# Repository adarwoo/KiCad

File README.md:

# KiCad
All KiCad projects

Adding all KiCad projects.

Currently, PCBs for the cnc (see Youtube guillaume.arreckx channel) are publised.

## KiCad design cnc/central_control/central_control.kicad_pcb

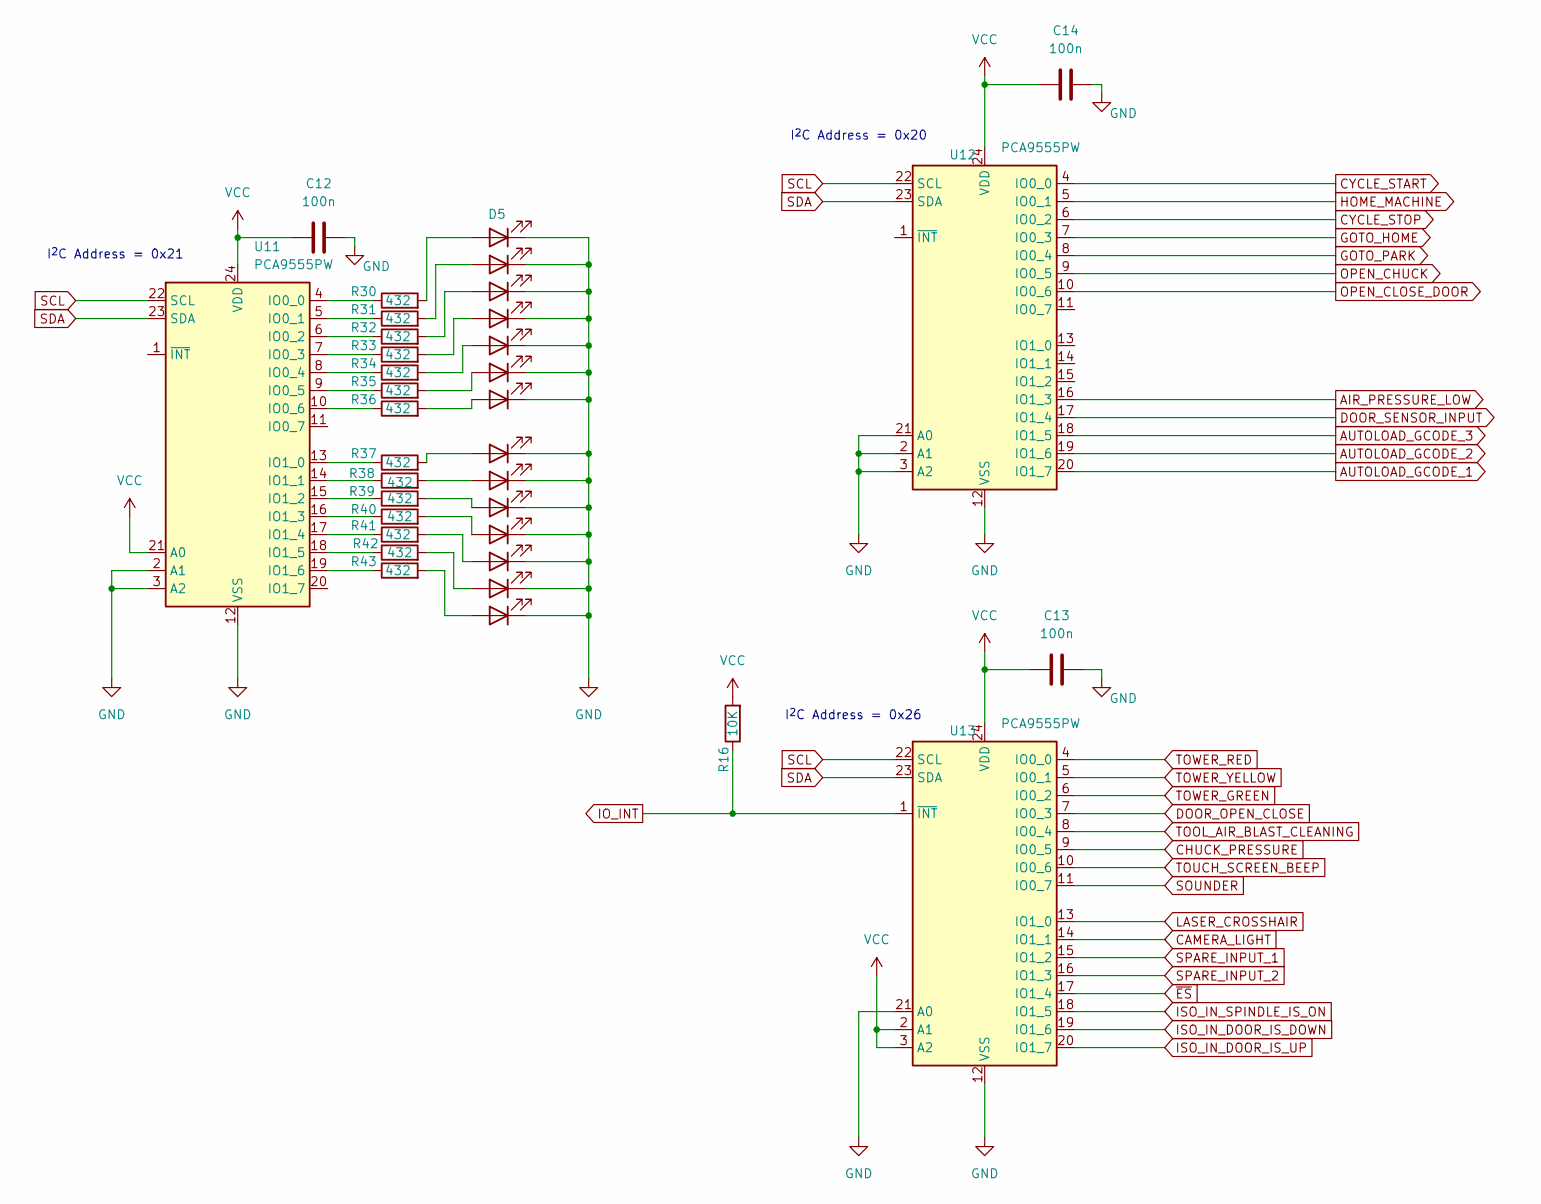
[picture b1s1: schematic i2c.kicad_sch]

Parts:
C12, C13, C14: 100n; C_0603_1608Metric_Pad1.08x0.95mm_HandSolder
D5: GRN; LED_D3.0mm
D6, D7, D8, D9, D10, D11, D12, D13, D14, D15, D16, D17, D18: LED; LED_D3.0mm
R16: 10K; R_1206_3216Metric_Pad1.30x1.75mm_HandSolder
R30, R31, R32, R33, R34, R35, R36, R37, R38, R39, R40, R41, R42, R43: 432; R_1206_3216Metric_Pad1.30x1.75mm_HandSolder
U11, U12, U13: PCA9555PW; TSSOP-24_4.4x7.8mm_P0.65mm

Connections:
AIR_PRESSURE_LOW: U12.16 (IO1_3); also elsewhere on the board
AUTOLOAD_GCODE_1: U12.20 (IO1_7); also elsewhere on the board
AUTOLOAD_GCODE_2: U12.19 (IO1_6); also elsewhere on the board
AUTOLOAD_GCODE_3: U12.18 (IO1_5); also elsewhere on the board
CAMERA_LIGHT: U13.14 (IO1_1); also elsewhere on the board
CHUCK_PRESSURE: U13.9 (IO0_5); also elsewhere on the board
CYCLE_START: U12.4 (IO0_0); also elsewhere on the board
CYCLE_STOP: U12.6 (IO0_2); also elsewhere on the board
DOOR_OPEN_CLOSE: U13.7 (IO0_3); also elsewhere on the board
DOOR_SENSOR_INPUT: U12.17 (IO1_4); also elsewhere on the board
GND: C12.2, C13.2, C14.2, D5.1 (K), D6.1 (K), D7.1 (K), D8.1 (K), D9.1 (K), D10.1 (K), D11.1 (K), D12.1 (K), D13.1 (K), D14.1 (K), D15.1 (K), D16.1 (K), D17.1 (K), D18.1 (K), U11.2 (A1), U11.3 (A2), U11.12 (VSS), U12.2 (A1), U12.3 (A2), U12.12 (VSS), U12.21 (A0), U13.12 (VSS), U13.21 (A0); also elsewhere on the board
GOTO_HOME: U12.7 (IO0_3); also elsewhere on the board
GOTO_PARK: U12.8 (IO0_4); also elsewhere on the board
HOME_MACHINE: U12.5 (IO0_1); also elsewhere on the board
ISO_IN_DOOR_IS_DOWN: U13.19 (IO1_6); also elsewhere on the board
ISO_IN_DOOR_IS_UP: U13.20 (IO1_7); also elsewhere on the board
ISO_IN_SPINDLE_IS_ON: U13.18 (IO1_5); also elsewhere on the board
LASER_CROSSHAIR: U13.13 (IO1_0); also elsewhere on the board
unnamed: D5.2 (A), R30.2
unnamed: D6.2 (A), R31.2
unnamed: D7.2 (A), R32.2
unnamed: D8.2 (A), R33.2
unnamed: D9.2 (A), R34.2
unnamed: D10.2 (A), R35.2
unnamed: D11.2 (A), R36.2
unnamed: D12.2 (A), R37.2
unnamed: D13.2 (A), R38.2
unnamed: D14.2 (A), R39.2
unnamed: D15.2 (A), R40.2
unnamed: D16.2 (A), R41.2
unnamed: D17.2 (A), R42.2
unnamed: D18.2 (A), R43.2
unnamed: R30.1, U11.4 (IO0_0)
unnamed: R31.1, U11.5 (IO0_1)
unnamed: R32.1, U11.6 (IO0_2)
unnamed: R33.1, U11.7 (IO0_3)
unnamed: R34.1, U11.8 (IO0_4)
unnamed: R35.1, U11.9 (IO0_5)
unnamed: R36.1, U11.10 (IO0_6)
unnamed: R37.1, U11.13 (IO1_0)
unnamed: R38.1, U11.14 (IO1_1)
unnamed: R39.1, U11.15 (IO1_2)
unnamed: R40.1, U11.16 (IO1_3)
unnamed: R41.1, U11.17 (IO1_4)
unnamed: R42.1, U11.18 (IO1_5)
unnamed: R43.1, U11.19 (IO1_6)
OPEN_CHUCK: U12.9 (IO0_5); also elsewhere on the board
OPEN_CLOSE_DOOR: U12.10 (IO0_6); also elsewhere on the board
SCL: U11.22 (SCL), U12.22 (SCL), U13.22 (SCL); also elsewhere on the board
SDA: U11.23 (SDA), U12.23 (SDA), U13.23 (SDA); also elsewhere on the board
SOUNDER: U13.11 (IO0_7); also elsewhere on the board
SPARE_INPUT_1: U13.15 (IO1_2); also elsewhere on the board
SPARE_INPUT_2: U13.16 (IO1_3); also elsewhere on the board
TOOL_AIR_BLAST_CLEANING: U13.8 (IO0_4); also elsewhere on the board
TOUCH_SCREEN_BEEP: U13.10 (IO0_6); also elsewhere on the board
TOWER_GREEN: U13.6 (IO0_2); also elsewhere on the board
TOWER_RED: U13.4 (IO0_0); also elsewhere on the board
TOWER_YELLOW: U13.5 (IO0_1); also elsewhere on the board
~ES: U13.17 (IO1_4); also elsewhere on the board

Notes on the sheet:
I^{2}C Address = 0x21
I^{2}C Address = 0x20
I^{2}C Address = 0x26

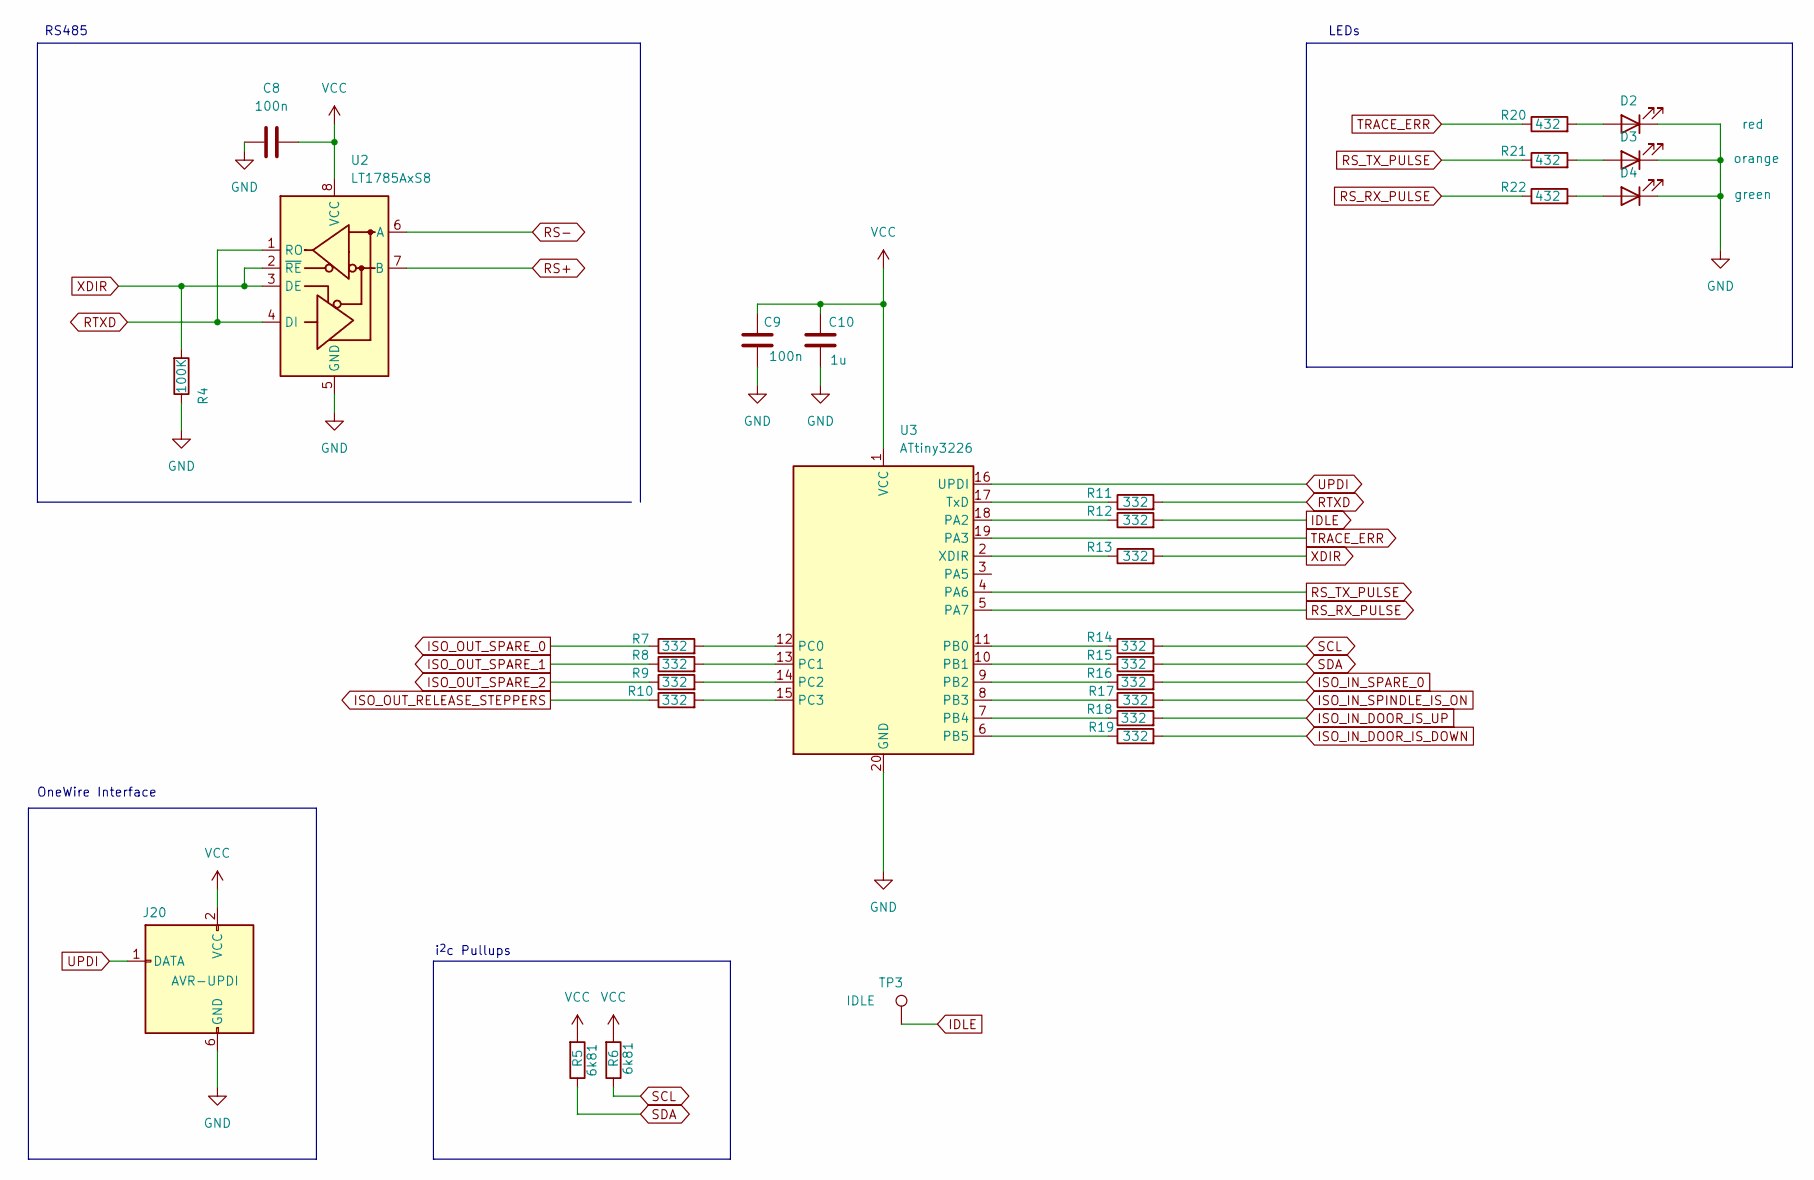
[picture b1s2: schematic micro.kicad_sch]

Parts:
C8: 100n; C_0603_1608Metric_Pad1.08x0.95mm_HandSolder
C9: 100n; C_0805_2012Metric_Pad1.18x1.45mm_HandSolder
C10: 1u; C_0805_2012Metric_Pad1.18x1.45mm_HandSolder
D2: red; LED_D3.0mm
D3: orange; LED_D3.0mm
D4: green; LED_D3.0mm
J20: AVR-UPDI; PinHeader_2x03_P2.54mm_Vertical
R4: 100K; R_1206_3216Metric_Pad1.30x1.75mm_HandSolder
R5, R6: 6k81; R_1206_3216Metric_Pad1.30x1.75mm_HandSolder
R7, R8, R9, R10, R11, R12, R13, R14, R15, R16, R17, R18, R19: 332; R_1206_3216Metric_Pad1.30x1.75mm_HandSolder
R20, R21, R22: 432; R_1206_3216Metric_Pad1.30x1.75mm_HandSolder
TP3: IDLE; TestPoint_Loop_D3.50mm_Drill0.9mm_Beaded
U2: LT1785AxS8; SOIC-8_3.9x4.9mm_P1.27mm
U3: ATtiny3226; SOIC-20W_7.5x12.8mm_P1.27mm

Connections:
GND: C8.1, C9.2, C10.2, D2.1 (K), D3.1 (K), D4.1 (K), J20.6 (GND), R4.1, U2.5 (GND), U3.20 (GND); also elsewhere on the board
IDLE: R12.2, TP3.1
ISO_OUT_CAMERA_LIGHT: R9.2, U3.14 (PC2); also elsewhere on the board
ISO_OUT_LASER_CROSS: R8.2, U3.13 (PC1); also elsewhere on the board
ISO_OUT_RELEASE_STEPPERS: R7.2, U3.12 (PC0); also elsewhere on the board
ISO_OUT_TOWER_LIGHT_GREEN: R19.1, U3.6 (PB5); also elsewhere on the board
ISO_OUT_TOWER_LIGHT_YELLOW: R18.1, U3.7 (PB4); also elsewhere on the board
unnamed: D2.2 (A), R20.2
unnamed: D3.2 (A), R21.2
unnamed: D4.2 (A), R22.2
unnamed: R10.2, U3.15 (PC3)
unnamed: R12.1, U3.18 (PA2)
unnamed: R14.1, U3.11 (PB0)
unnamed: R15.1, U3.10 (PB1)
unnamed: R11.1, U3.17 (TxD)
unnamed: R13.1, U3.2 (XDIR)
RS+: U2.7 (B); also elsewhere on the board
RS-: U2.6 (A); also elsewhere on the board
RS_RX_PULSE: R22.1, U3.5 (PA7)
RS_TX_PULSE: R21.1, U3.4 (PA6)
RTXD: R11.2, U2.1 (RO), U2.4 (DI)
SCL: R6.1, R14.2; also elsewhere on the board
SDA: R5.1, R15.2; also elsewhere on the board
TRACE_ERR: R20.1, U3.19 (PA3)
UPDI: J20.1 (DATA), U3.16 (UPDI)
XDIR: R4.2, R13.2, U2.2 (~RE), U2.3 (DE)

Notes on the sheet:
LEDs
i^{2}c Pullups
OneWire Interface
RS485

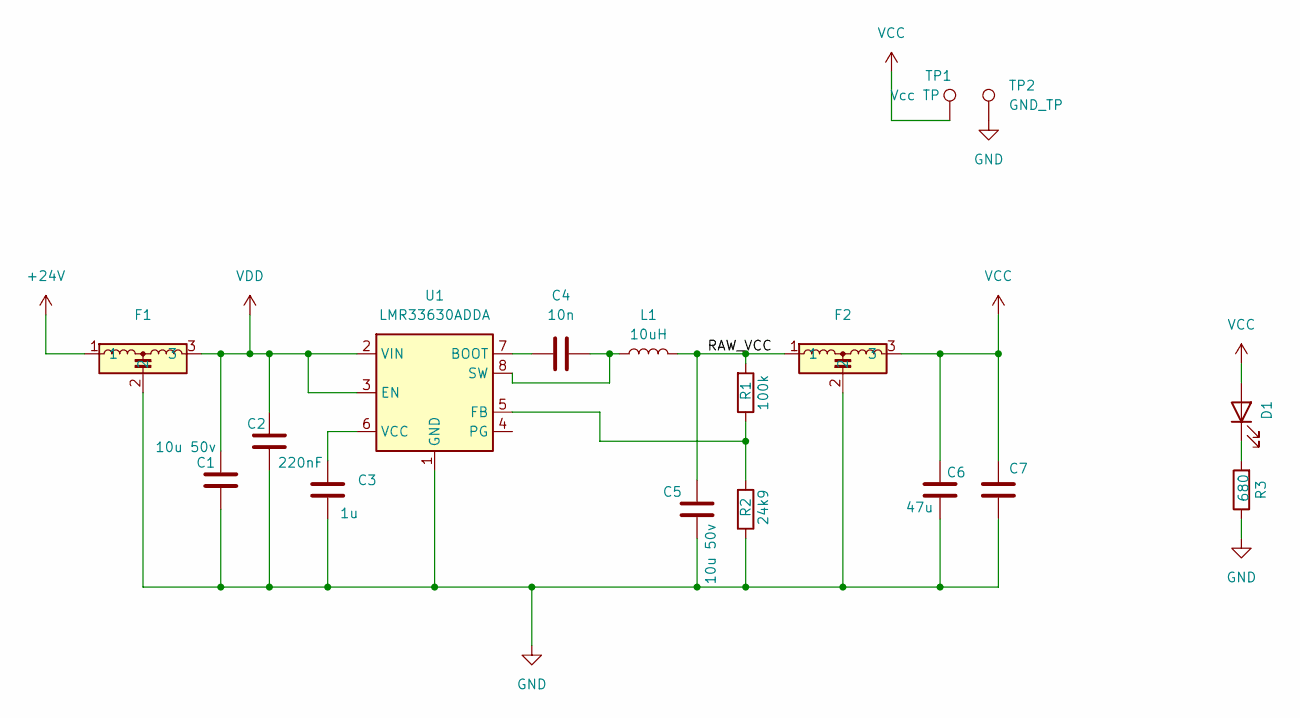
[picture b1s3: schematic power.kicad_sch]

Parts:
C1, C5: 10u 50v; C_1210_3225Metric_Pad1.33x2.70mm_HandSolder
C2: 220nF; C_0805_2012Metric_Pad1.18x1.45mm_HandSolder
C3: 1u; C_0805_2012Metric_Pad1.18x1.45mm_HandSolder
C4: 10n; C_0805_2012Metric_Pad1.18x1.45mm_HandSolder
C6: 47u; C_1210_3225Metric_Pad1.33x2.70mm_HandSolder
C7: 100n; C_0603_1608Metric_Pad1.08x0.95mm_HandSolder
D1: LED; LED_D3.0mm
F1, F2: Murata_NFM61R
L1: 10uH; L_Wuerth_HCM-7070
R1: 100k; R_0603_1608Metric_Pad0.98x0.95mm_HandSolder
R2: 24k9; R_0603_1608Metric_Pad0.98x0.95mm_HandSolder
R3: 680; R_1206_3216Metric_Pad1.30x1.75mm_HandSolder
TP1: Vcc TP; TestPoint_Loop_D3.50mm_Drill0.9mm_Beaded
TP2: GND_TP; TestPoint_Loop_D3.50mm_Drill0.9mm_Beaded
U1: LMR33630ADDA; Texas_HSOP-8-1EP_3.9x4.9mm_P1.27mm_ThermalVias

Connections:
+24V: F1.1; also elsewhere on the board
/Power supply/RAW_VCC: C5.1, F2.1, L1.2, R1.2
GND: C1.2, C2.2, C3.2, C5.2, C6.2, C7.1, F1.2, F2.2, R2.1, R3.1, TP2.1, U1.1 (GND), U1.9 (GND); also elsewhere on the board
unnamed: D1.1 (K), R3.2
unnamed: C4.1, U1.7 (BOOT)
unnamed: R1.1, R2.2, U1.5 (FB)
unnamed: C4.2, L1.1, U1.8 (SW)
unnamed: C3.1, U1.6 (VCC)
VDD: C1.1, C2.1, F1.3, U1.2 (VIN), U1.3 (EN)

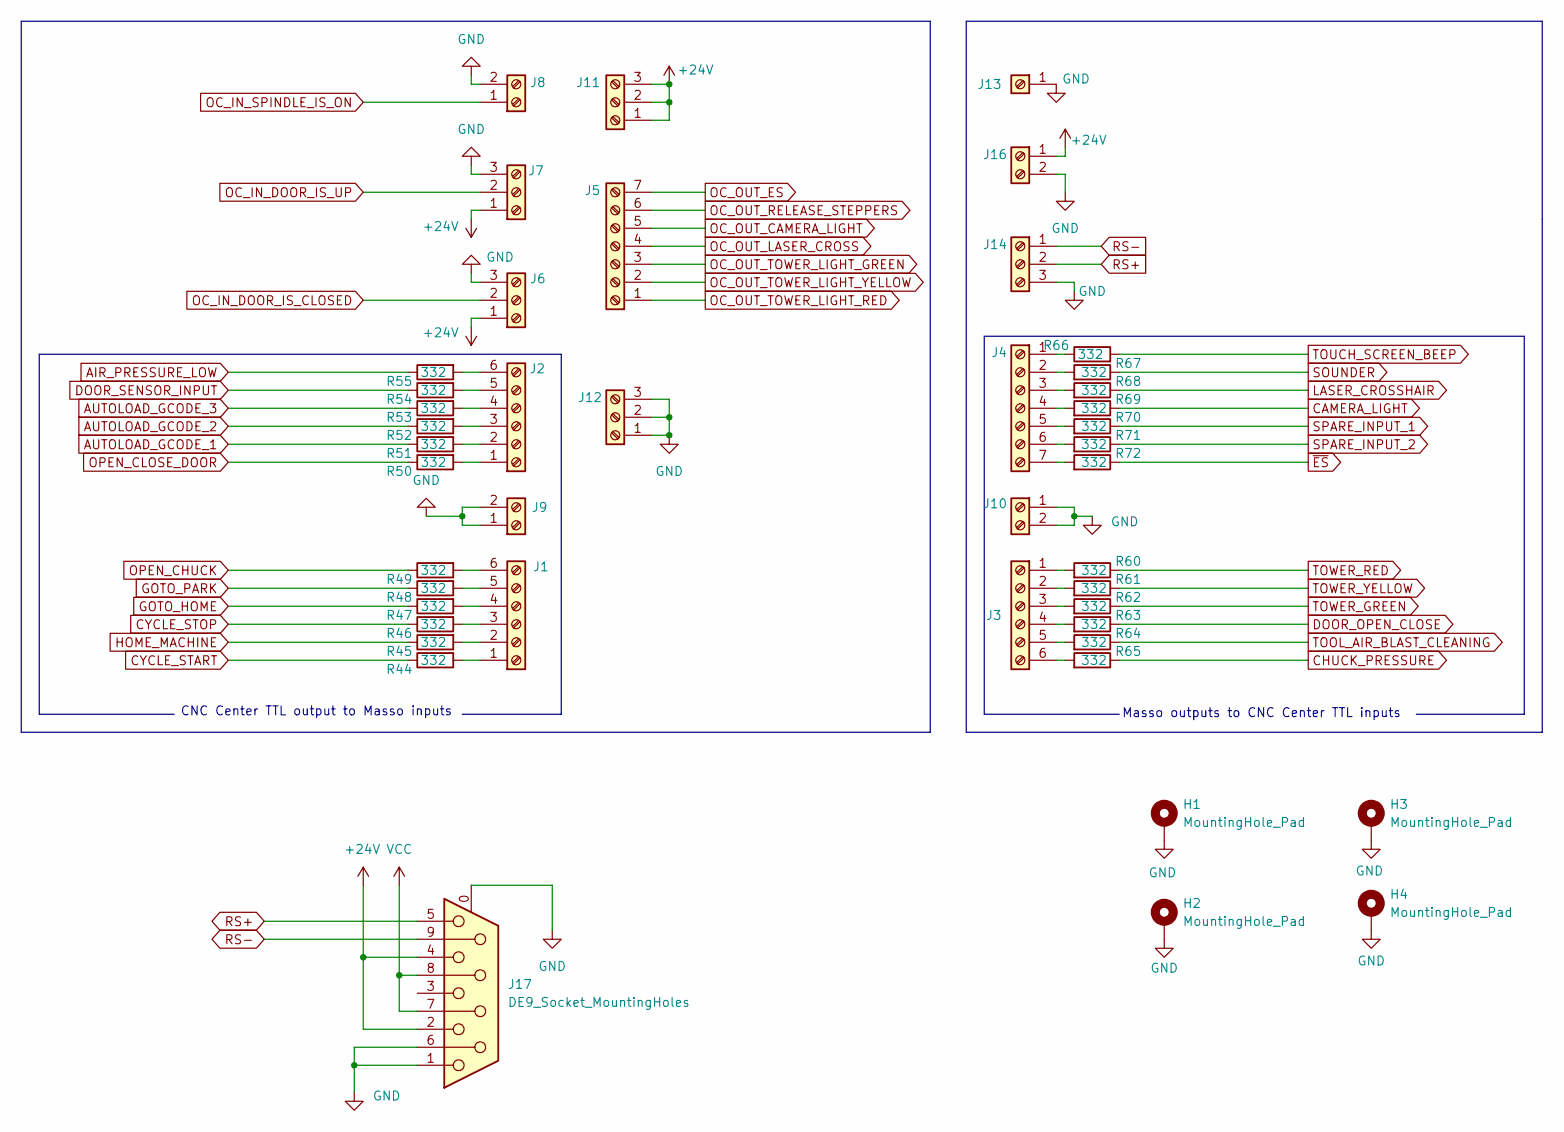
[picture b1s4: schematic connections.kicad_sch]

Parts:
H1, H2, H3, H4: MountingHole_Pad; MountingHole_3.2mm_M3_DIN965_Pad_TopBottom
J1, J2, J3: 6pins; PhoenixContact_MCV_1,5_6-G-3.81_1x06_P3.81mm_Vertical
J4, J5: 7pins; PhoenixContact_MCV_1,5_7-G-3.81_1x07_P3.81mm_Vertical
J6, J7, J11, J12, J14: 3pins; PhoenixContact_MCV_1,5_3-G-3.81_1x03_P3.81mm_Vertical
J8, J9, J10, J16: Phoenix; PhoenixContact_MCV_1,5_2-G-3.81_1x02_P3.81mm_Vertical
J13: GroundPlot
J17: DE9_Socket_MountingHoles; DSUB-9_Pins_Vertical_P2.77x2.84mm_MountingHoles
R44, R45, R46, R47, R48, R49, R50, R51, R52, R53, R54, R55, R60, R61, R62, R63, R64, R65, R66, R67, R68, R69, R70, R71, R72: 332; R_1206_3216Metric_Pad1.30x1.75mm_HandSolder

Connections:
+24V: J6.1, J7.1, J11.1, J11.2, J11.3, J16.1, J17.2, J17.4; also elsewhere on the board
AIR_PRESSURE_LOW: R55.1; also elsewhere on the board
AUTOLOAD_GCODE_1: R51.1; also elsewhere on the board
AUTOLOAD_GCODE_2: R52.1; also elsewhere on the board
AUTOLOAD_GCODE_3: R53.1; also elsewhere on the board
CAMERA_LIGHT: R69.1; also elsewhere on the board
CHUCK_PRESSURE: R65.1; also elsewhere on the board
CYCLE_START: R44.1; also elsewhere on the board
CYCLE_STOP: R46.1; also elsewhere on the board
DOOR_OPEN_CLOSE: R63.1; also elsewhere on the board
DOOR_SENSOR_INPUT: R54.1; also elsewhere on the board
GND: H1.1, H2.1, H3.1, H4.1, J6.3, J7.3, J8.2, J9.1, J9.2, J10.1, J10.2, J12.1, J12.2, J12.3, J13.1, J14.3, J16.2, J17.0 (PAD), J17.1, J17.6; also elsewhere on the board
GOTO_HOME: R47.1; also elsewhere on the board
GOTO_PARK: R48.1; also elsewhere on the board
HOME_MACHINE: R45.1; also elsewhere on the board
LASER_CROSSHAIR: R68.1; also elsewhere on the board
unnamed: J1.1, R44.2
unnamed: J1.2, R45.2
unnamed: J1.3, R46.2
unnamed: J1.4, R47.2
unnamed: J1.5, R48.2
unnamed: J1.6, R49.2
unnamed: J2.1, R50.2
unnamed: J2.2, R51.2
unnamed: J2.3, R52.2
unnamed: J2.4, R53.2
unnamed: J2.5, R54.2
unnamed: J2.6, R55.2
unnamed: J3.1, R60.2
unnamed: J3.2, R61.2
unnamed: J3.3, R62.2
unnamed: J3.4, R63.2
unnamed: J3.5, R64.2
unnamed: J3.6, R65.2
unnamed: J4.1, R66.1
unnamed: J4.2, R67.2
unnamed: J4.3, R68.2
unnamed: J4.4, R69.2
unnamed: J4.5, R70.2
unnamed: J4.6, R71.2
unnamed: J4.7, R72.2
OC_IN_DOOR_IS_CLOSED: J6.2; also elsewhere on the board
OC_IN_DOOR_IS_UP: J7.2; also elsewhere on the board
OC_IN_SPINDLE_IS_ON: J8.1; also elsewhere on the board
OC_OUT_CAMERA_LIGHT: J5.5; also elsewhere on the board
OC_OUT_ES: J5.7; also elsewhere on the board
OC_OUT_LASER_CROSS: J5.4; also elsewhere on the board
OC_OUT_RELEASE_STEPPERS: J5.6; also elsewhere on the board
OC_OUT_TOWER_LIGHT_GREEN: J5.3; also elsewhere on the board
OC_OUT_TOWER_LIGHT_RED: J5.1; also elsewhere on the board
OC_OUT_TOWER_LIGHT_YELLOW: J5.2; also elsewhere on the board
OPEN_CHUCK: R49.1; also elsewhere on the board
OPEN_CLOSE_DOOR: R50.1; also elsewhere on the board
RS+: J14.2, J17.5; also elsewhere on the board
RS-: J14.1, J17.9; also elsewhere on the board
SOUNDER: R67.1; also elsewhere on the board
SPARE_INPUT_1: R70.1; also elsewhere on the board
SPARE_INPUT_2: R71.1; also elsewhere on the board
TOOL_AIR_BLAST_CLEANING: R64.1; also elsewhere on the board
TOUCH_SCREEN_BEEP: R66.2; also elsewhere on the board
TOWER_GREEN: R62.1; also elsewhere on the board
TOWER_RED: R60.1; also elsewhere on the board
TOWER_YELLOW: R61.1; also elsewhere on the board
~ES: R72.1; also elsewhere on the board

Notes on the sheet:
CNC Center TTL output to Masso inputs
Masso outputs to CNC Center TTL inputs

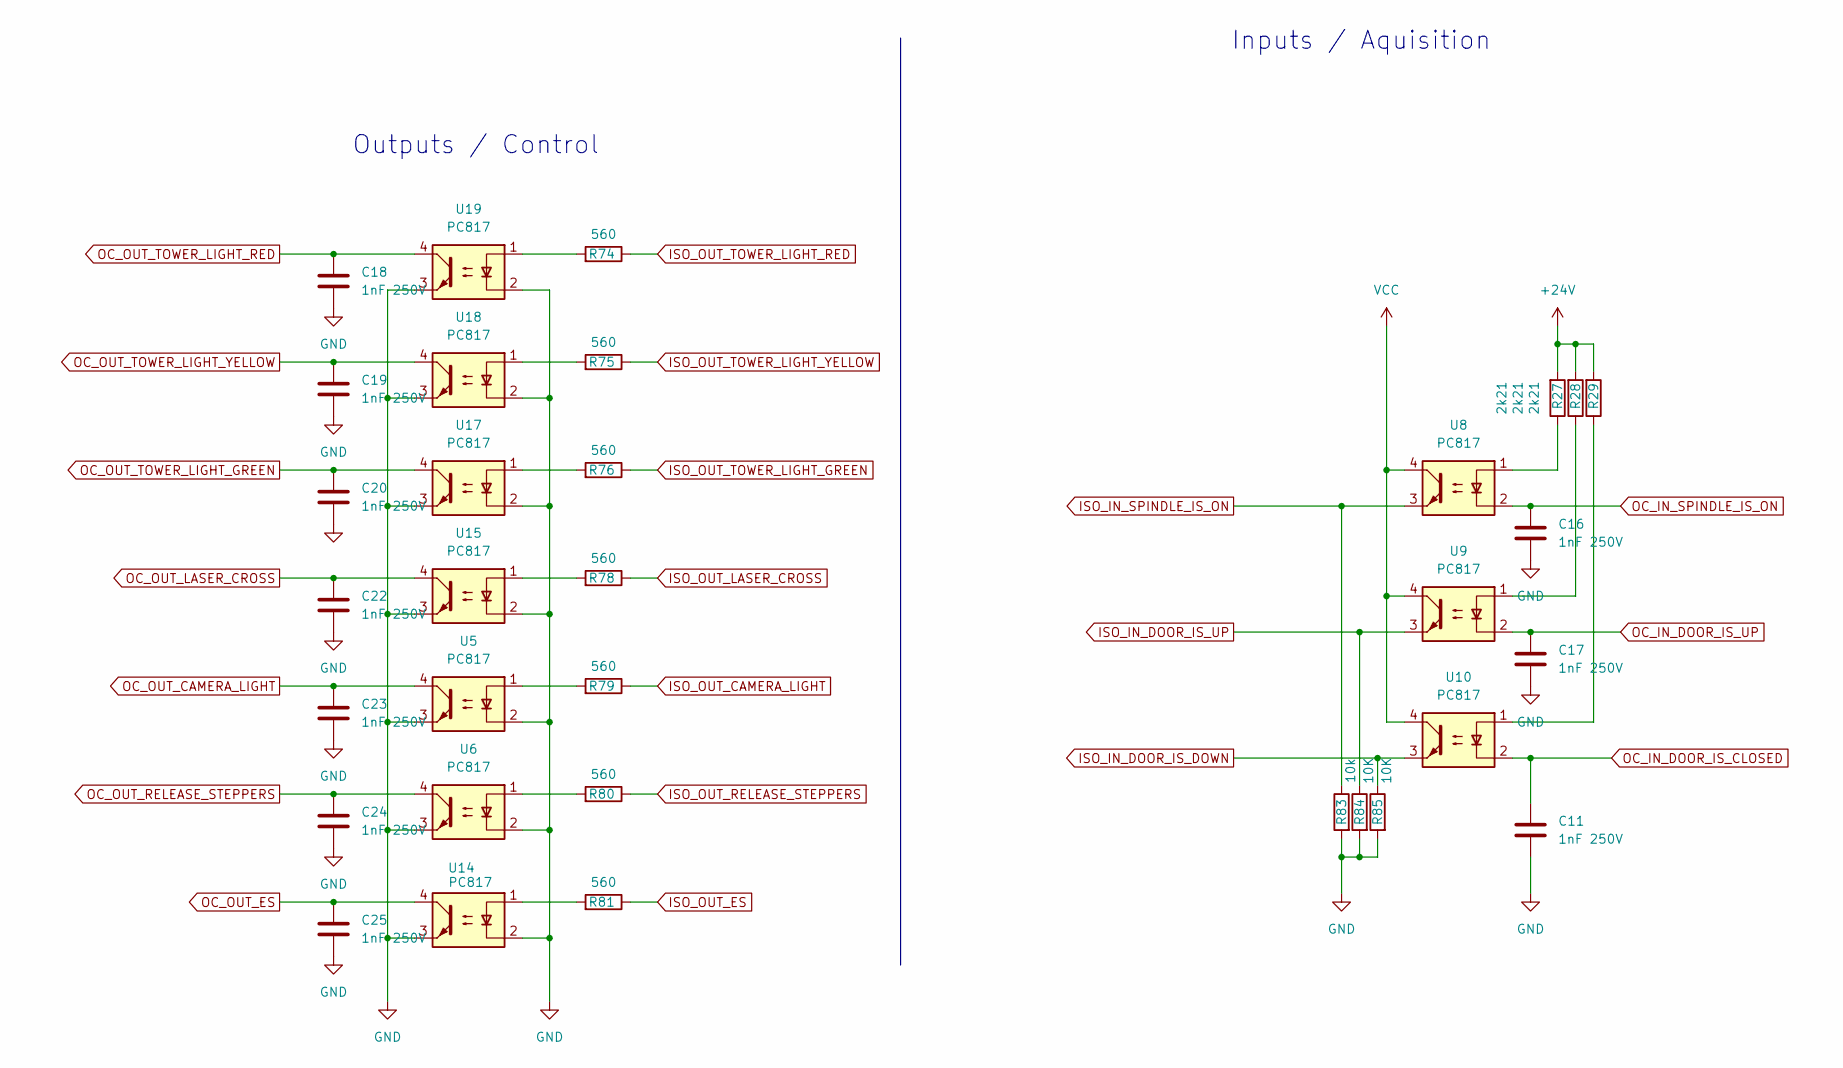
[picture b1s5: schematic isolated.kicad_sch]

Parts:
C11, C16, C17, C18, C19, C20, C22, C23, C24, C25: 1nF 250V; C_1206_3216Metric_Pad1.33x1.80mm_HandSolder
R27, R28, R29: 2k21; R_1206_3216Metric_Pad1.30x1.75mm_HandSolder
R74, R75, R76, R78, R79, R80, R81: 560; R_1206_3216Metric_Pad1.30x1.75mm_HandSolder
R83: 10k; R_1206_3216Metric_Pad1.30x1.75mm_HandSolder
R84, R85: 10K; R_1206_3216Metric_Pad1.30x1.75mm_HandSolder
U5, U6, U8, U9, U10, U14, U15, U17, U18, U19: PC817; DIP-4_W7.62mm

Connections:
+24V: R27.2, R28.2, R29.2; also elsewhere on the board
GND: C11.2, C16.2, C17.2, C18.2, C19.2, C20.2, C22.2, C23.2, C24.2, C25.2, R83.2, R84.2, R85.2, U5.2, U5.3, U6.2, U6.3, U14.2, U14.3, U15.2, U15.3, U17.2, U17.3, U18.2, U18.3, U19.2, U19.3; also elsewhere on the board
ISO_IN_DOOR_IS_DOWN: R85.1, U10.3; also elsewhere on the board
ISO_IN_DOOR_IS_UP: R84.1, U9.3; also elsewhere on the board
ISO_IN_SPINDLE_IS_ON: R83.1, U8.3; also elsewhere on the board
ISO_OUT_CAMERA_LIGHT: R79.1; also elsewhere on the board
ISO_OUT_LASER_CROSS: R78.1; also elsewhere on the board
ISO_OUT_RELEASE_STEPPERS: R80.1; also elsewhere on the board
ISO_OUT_TOWER_LIGHT_GREEN: R76.1; also elsewhere on the board
ISO_OUT_TOWER_LIGHT_YELLOW: R75.1; also elsewhere on the board
unnamed: R27.1, U8.1
unnamed: R28.1, U9.1
unnamed: R29.1, U10.1
unnamed: R74.2, U19.1
unnamed: R75.2, U18.1
unnamed: R76.2, U17.1
unnamed: R78.2, U15.1
unnamed: R79.2, U5.1
unnamed: R80.2, U6.1
unnamed: R81.2, U14.1
OC_IN_DOOR_IS_CLOSED: C11.1, U10.2; also elsewhere on the board
OC_IN_DOOR_IS_UP: C17.1, U9.2; also elsewhere on the board
OC_IN_SPINDLE_IS_ON: C16.1, U8.2; also elsewhere on the board
OC_OUT_CAMERA_LIGHT: C23.1, U5.4; also elsewhere on the board
OC_OUT_ES: C25.1, U14.4; also elsewhere on the board
OC_OUT_LASER_CROSS: C22.1, U15.4; also elsewhere on the board
OC_OUT_RELEASE_STEPPERS: C24.1, U6.4; also elsewhere on the board
OC_OUT_TOWER_LIGHT_GREEN: C20.1, U17.4; also elsewhere on the board
OC_OUT_TOWER_LIGHT_RED: C18.1, U19.4; also elsewhere on the board
OC_OUT_TOWER_LIGHT_YELLOW: C19.1, U18.4; also elsewhere on the board

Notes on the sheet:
Inputs / Aquisition
Outputs / Control

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
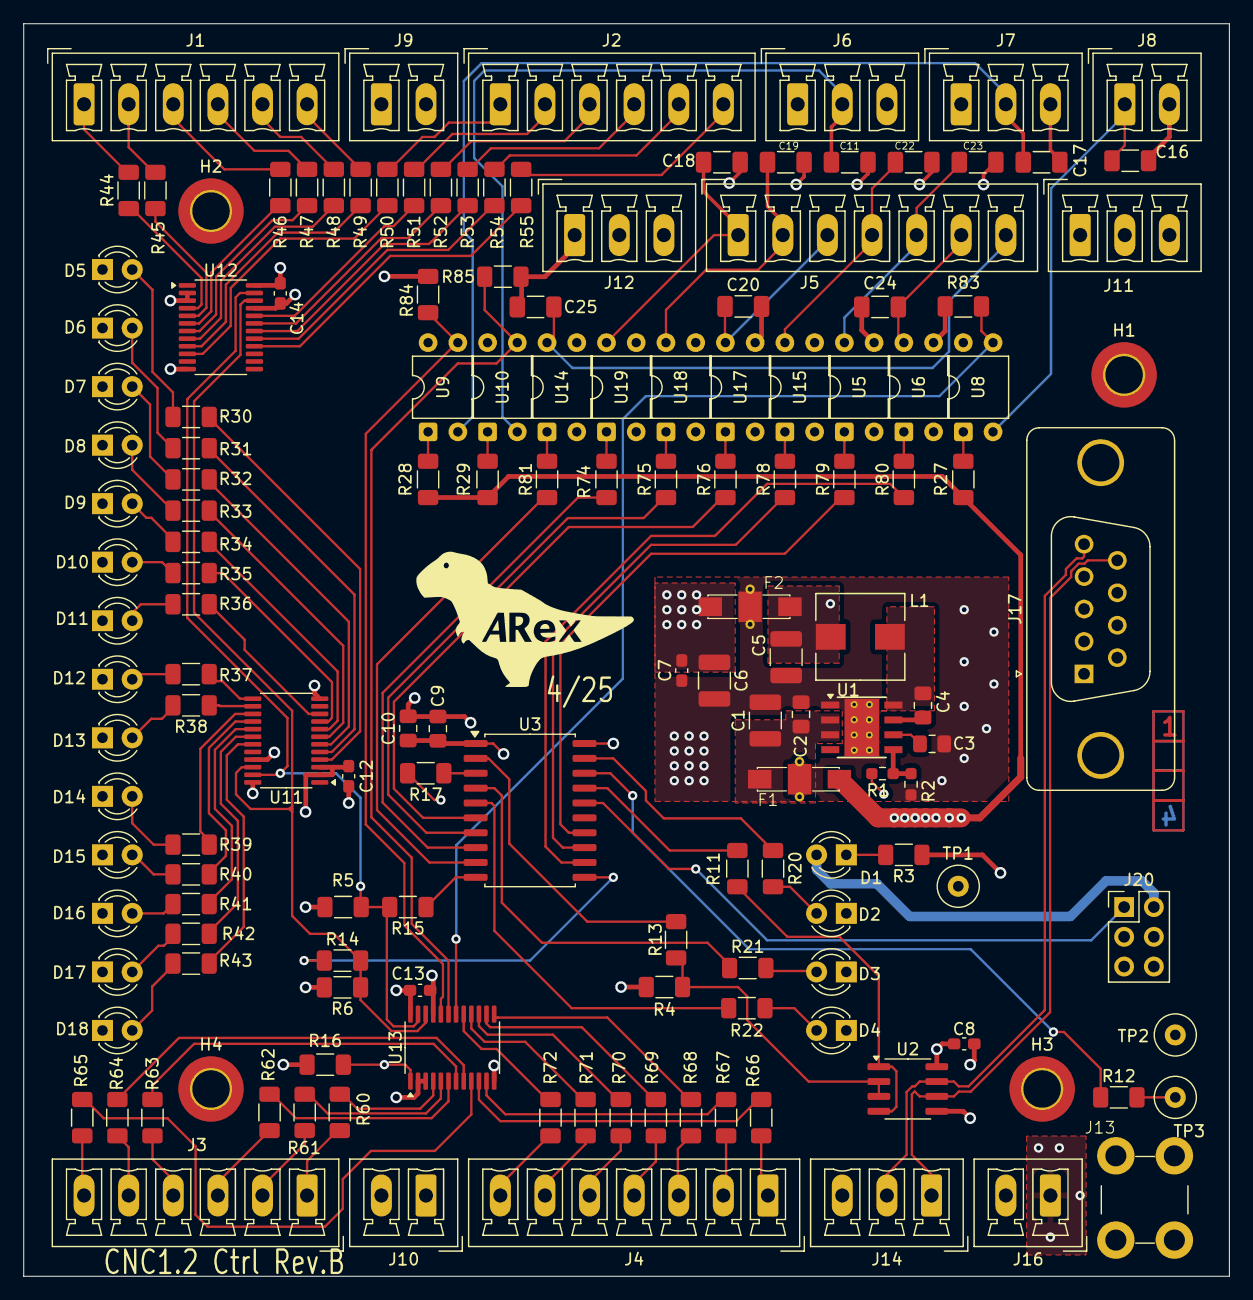
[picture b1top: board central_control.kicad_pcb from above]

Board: 4 copper layers, 103.0 x 107.0 mm, 152 parts (0 on the bottom side), 139 nets.

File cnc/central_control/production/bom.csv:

Designator,Footprint,Quantity,Value,LCSC Part #
"C1, C5",1210,2,10u 50v,
"C10, C3",0805,2,1u,
"C11, C16, C17, C18, C19, C20, C22, C23, C24, C25",1206,10,1nF 250V,
"C12, C13, C14, C7, C8",0603,5,100n,
C2,0805,1,220nF,
C4,0805,1,10n,
C6,1210,1,47u,
C9,0805,1,100n,
"D1, D10, D11, D12, D13, D14, D15, D16, D17, D18, D6, D7, D8, D9",LED_D3.0mm,14,LED,
D2,LED_D3.0mm,1,red,
D3,LED_D3.0mm,1,orange,
D4,LED_D3.0mm,1,green,
D5,LED_D3.0mm,1,GRN,
"F1, F2",Murata_NFM61R,2,~,
"J1, J2, J3","PhoenixContact_MCV_1,5_6-G-3.81_1x06_P3.81mm_Vertical",3,6pins,
"J10, J16, J8, J9","PhoenixContact_MCV_1,5_2-G-3.81_1x02_P3.81mm_Vertical",4,Phoenix,
"J11, J12, J14, J6, J7","PhoenixContact_MCV_1,5_3-G-3.81_1x03_P3.81mm_Vertical",5,3pins,
J13,GroundPlot,1,~,
J17,DSUB-9_Pins_Vertical_P2.77x2.84mm_MountingHoles,1,DE9_Socket_MountingHoles,
J20,PinHeader_2x03_P2.54mm_Vertical,1,AVR-UPDI,
"J4, J5","PhoenixContact_MCV_1,5_7-G-3.81_1x07_P3.81mm_Vertical",2,7pins,
L1,L_Wuerth_HCM-7070,1,10uH,
R1,0603,1,100k,
"R11, R12, R13, R14, R15, R17, R44, R45, R46, R47, R48, R49, R50, R51, R52, R53, R54, R55, R60, R61, R62, R63, R64, R65, R66, R67, R68, R69, R70, R71, R72",1206,31,332,
"R16, R83, R84, R85",1206,4,10K,
R2,0603,1,24k9,
"R20, R21, R22, R30, R31, R32, R33, R34, R35, R36, R37, R38, R39, R40, R41, R42, R43",1206,17,432,
"R27, R28, R29",1206,3,2k21,
R3,1206,1,680,
R4,1206,1,100K,
"R5, R6",1206,2,6k81,
"R74, R75, R76, R78, R79, R80, R81",1206,7,560,
TP1,TestPoint_Loop_D3.50mm_Drill0.9mm_Beaded,1,Vcc TP,
TP2,TestPoint_Loop_D3.50mm_Drill0.9mm_Beaded,1,GND_TP,
TP3,TestPoint_Loop_D3.50mm_Drill0.9mm_Beaded,1,IDLE,
U1,Texas_HSOP-8-1EP_3.9x4.9mm_P1.27mm_ThermalVias,1,LMR33630ADDA,
"U10, U14, U15, U17, U18, U19, U5, U6, U8, U9",DIP-4_W7.62mm,10,PC817,
"U11, U12, U13",TSSOP-24_4.4x7.8mm_P0.65mm,3,PCA9555PW,
U2,SOIC-8_3.9x4.9mm_P1.27mm,1,LT1785AxS8,
U3,SOIC-20W_7.5x12.8mm_P1.27mm,1,ATtiny3226,
